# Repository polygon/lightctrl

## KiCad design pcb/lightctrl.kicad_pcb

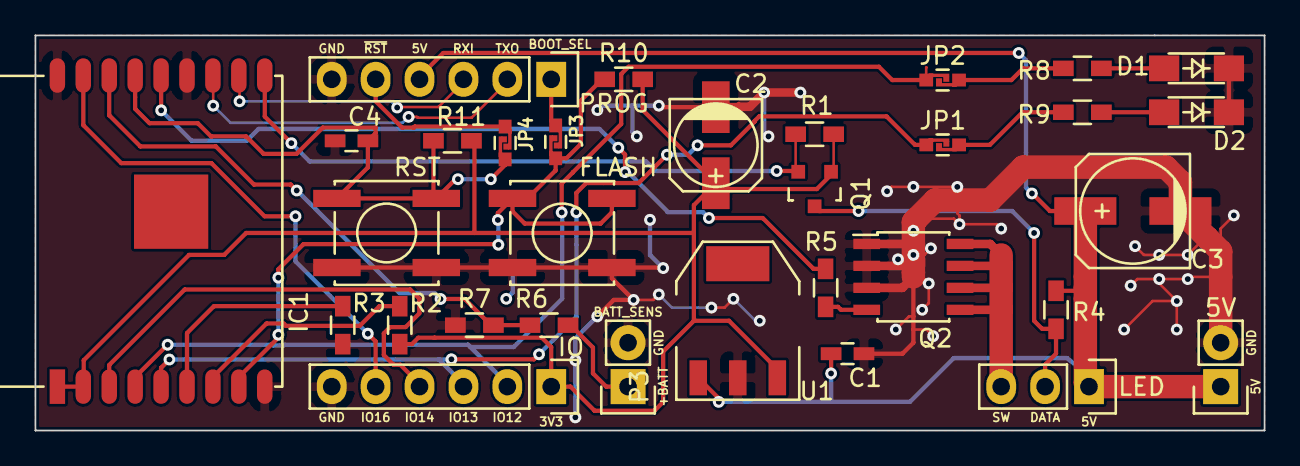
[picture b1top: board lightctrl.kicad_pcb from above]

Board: 2 copper layers, 71.1 x 22.9 mm, 32 parts (0 on the bottom side), 26 nets.

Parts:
C1: 470n; C_0603_HandSoldering
C2: 33u; c_elec_5x5.3
C3: 100u; c_elec_6.3x7.7
C4: 100n; C_0603_HandSoldering
D1, D2: LED; LED_3.2x1.6
IC1: ESP-WROOM-02; ESP-13-WROOM-02
JP1, JP2, JP3, JP4: JUMPER; SOLDER_JUMPER
P1: LED_CONN; Pin_Header_Straight_1x03
P2: PROG; Pin_Header_Straight_1x06
P3: IO; Pin_Header_Straight_1x06
P4: BATT_SENSE; Pin_Header_Straight_1x02
P5: 5V; Pin_Header_Straight_1x02
Q1: BSS138; SOT-23
Q2: IRF8788; SOIC-8_3.9x4.9mm_Pitch1.27mm
R1, R4: 1K; R_0603_HandSoldering
R2, R10, R11: 4k7; R_0603_HandSoldering
R3: 10K; R_0603_HandSoldering
R5: 330; R_0603_HandSoldering
R6: 24k; R_0603_HandSoldering
R7: 2k; R_0603_HandSoldering
R8, R9: R; R_0603_HandSoldering
SW1: SW_FLASH; SW_SPST_EVPBF
SW2: SW_RST; SW_SPST_EVPBF
U1: LM3940; SOT-223

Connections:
+3V3: C2.1, IC1.1, IC1.2, P3.1, Q1.1, R1.2, R2.2, R10.2, R11.2, U1.3
+5V: C1.1, C3.1, P1.1, P2.4, P5.1, R4.1, U1.1
+BATT: P4.1, R6.1
/ESP8266/BOOT_SEL: IC1.8, JP3.1, R10.1, SW1.2
/ESP8266/CTS: JP4.2, P2.5
/ESP8266/DTR: JP3.2, P2.1
/ESP8266/IO12: IC1.4, JP2.1, P3.2
/ESP8266/IO13: IC1.5, JP1.1, P3.3
/ESP8266/IO14: IC1.3, P3.4
/ESP8266/IO16: IC1.17, P3.5
/ESP8266/LED_DATA: IC1.10, Q1.2, R1.1
/ESP8266/LED_PWR: IC1.14, R5.2
/ESP8266/RST: C4.1, IC1.15, JP4.1, R11.1, SW2.2
/ESP8266/RXI: IC1.12, P2.2
/ESP8266/TXO: IC1.11, P2.3
/ESP8266/WS2812_DATA: P1.2, Q1.3, R4.2
GND: C1.2, C2.2, C3.2, C4.2, D1.1, D2.1, IC1.9, IC1.13, IC1.18, P2.6, P3.6, P4.2, P5.2, Q2.1, Q2.2, Q2.3, R3.2, R7.2, SW1.1, SW2.1, U1.2
unnamed: D1.2, R8.2
unnamed: D2.2, R9.2
unnamed: IC1.6, R3.1
unnamed: IC1.7, R2.1
unnamed: IC1.16, R6.2, R7.1
unnamed: JP1.2, R9.1
unnamed: JP2.2, R8.1
unnamed: P1.3, Q2.5, Q2.6, Q2.7, Q2.8
unnamed: Q2.4, R5.1

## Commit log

2016-10-03 Initial circuit design, not finished
2016-10-03 Part libraries
2016-10-03 Fixed design
2016-10-03 Added parts
2016-10-03 Added gitignore
2016-10-03 Part footprints assigned completely
2016-10-03 Layout!!!1!
2016-10-03 Board!!!!1!!
2016-10-03 Thicker power traces
2016-10-03 New stick layout form
2016-10-04 Pre-Compactifying checkpoint
2016-10-04 Placement done
2016-10-04 Routing finished
2016-10-04 Silkscreen finished
2016-10-05 Fixing part names in PCB
2016-10-05 Pin header silkscreen, more ground vias
2016-10-05 Fixed bottom silkscreen text
    Moved text away from pin headers
2016-10-05 Replaced LED footprint with 3.2mmx1.6mm
    Reasonable LED part available with that footprint
2016-10-06 Routing and silkscreen fixes
2016-10-06 Separated routing of data and +5V
2016-10-06 GND connection improvements
2016-10-06 OSHPark preview images
2016-10-06 Silkscreen fixes at LEDs
2016-10-27 State as it is!
